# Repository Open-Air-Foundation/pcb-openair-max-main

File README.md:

# AirGradient Open Air Max — Hardware

> KiCad hardware design files for the [AirGradient Open Air Max](https://www.airgradient.com/professional/products/open-air-max/), a professional outdoor air quality monitor.

## Overview

Open Air Max is AirGradient's professional outdoor air quality monitor, designed for autonomous, off-grid operation. It measures PM2.5 (2× Plantower PMS5003), CO₂ (SenseAir Sunlight NDIR, 0–5,000 ppm), TVOCs/NOₓ (Sensirion SGP41), NO₂ (AlphaSense A43F) and O₃ (AlphaSense A431), plus temperature and humidity (Sensirion SHT40), in a UV-resistant, weatherproof ASA enclosure with wall or pole mounting (model O-M-1PPSTON-CE; CE, RoHS, REACH, and FCC certified).

Data is reported over Wi-Fi (2.4 GHz IEEE 802.11 b/g/n) or 4G cellular (LTE Cat 1). Power comes from a 10 W solar panel charging a user-replaceable pack of three 3,500 mAh Li-ion 18650 cells in series (3S), managed by a dedicated battery management system and a low-power design throughout.

This repository contains the monitor's main PCB: the ESP32-C6 MCU, solar/USB-C charging and power path, battery management, and the interfaces the sensor modules and the cellular CE card plug into — complete with schematics, PCB layout, bundled 3D models, and the production output set.

## Design structure

The design is a single 4-layer board (signal / power plane / ground plane / signal) drawn across three schematic sheets:

| Sheet | File | Contents |
|---|---|---|
| Root | `PCB/openair-max/One-Air-Max.kicad_sch` | MCU, power distribution, sensor and CE-card interfaces |
| Battery holder | `PCB/openair-max/Battery-Holder.kicad_sch` | 18650 battery interface and BMS |
| Solar module | `PCB/openair-max/Solar-Module.kicad_sch` | Charger and solar input conditioning |

## Repository structure

```
PCB/
└── openair-max/             # Main PCB (schematic, layout, DRC rules, production/)
libraries/                   # Shared 3D model libraries
├── 3d/                      # STEP models
└── easyeda2kicad/           # easyeda2kicad WRL models
```

## Key components

| Function | Part | Ref |
|---|---|---|
| MCU / Wi-Fi / BLE | ESP32-C6-WROOM-1-N8 | U1 |
| Buck converter | TPS62902 | U2 |
| Hardware watchdog timer | TPL5010 | U3 |
| Battery management system (BMS) | BQ7790512 (BQ76905 family) | U4 |
| Battery charger (solar + USB-C) | BQ25798 | U5 |
| Boost converter | TPS62903 | U6 |
| Power mux / load switch (RC soft-start) | TPS2117 | U7 |
| I²C-to-dual-UART bridge | WK2132 | U8 |
| EEPROM (2 Mbit, optional — DNP) | AT24CM02 | U12 |
| High-side load switches (switched sensor rails) | TPS27081A | U13–U19 |

**Power architecture:** The BQ25798 charger takes two power inputs — the solar cell on **VAC1** and USB-C on **VAC2** — and charges the 3S 18650 pack behind the BQ76905 BMS. The system rail is switched through the TPS2117 with an RC soft-start network to limit inrush current, and a 470 µF bulk capacitor ahead of the load switch provides brownout immunity.

## Plug-in modules

The gas sensors and the cellular option are separate boards that plug into this board's connectors. The assembled Open Air Max (O-M-1PPSTON-CE) carries all of them:

| Module | Repository | Connector on this board |
|---|---|---|
| SUNX CO₂ sensor module (SenseAir Sunlight, UART) | [pcb-module-sunx](https://github.com/Open-Air-Foundation/pcb-module-sunx) | `CO2` — 8-pin Molex PicoBlade: switched 5 V (VOUT2, EN_CO2 = IO5), GND, UART0 (IO0/IO1) |
| SGP41 TVOC/NOₓ sensor module (I²C) | [pcb-module-sgp41](https://github.com/Open-Air-Foundation/pcb-module-sgp41) | `I2C1` / `I2C2` — 1×4 sockets, 2.54 mm: 3.3 V, GND, SCL (IO6), SDA (IO7) |
| SHT4x temperature/humidity sensor module (I²C) | [pcb-module-sht40](https://github.com/Open-Air-Foundation/pcb-module-sht40) | `I2C1` / `I2C2` — the two sockets are identical; one takes the SGP41 module, the other the SHT4x module |
| AlphaSense ADC module — NO₂ (A43F) and O₃ (A431), I²C | [pcb-module-alphasense-adc](https://github.com/Open-Air-Foundation/pcb-module-alphasense-adc) | `NO2` — 8-pin Molex PicoBlade: switched 5 V and 3.3 V (VOUT6/VOUT5, EN_NO2 = IO4), GND, I²C |
| CE card — 4G cellular (LTE Cat 1) | [pcb-module-ce-card](https://github.com/Open-Air-Foundation/pcb-module-ce-card) | `CE1` — 8-pin Molex PicoBlade: switched 5 V and 3.3 V (VOUT4/VOUT3, EN_CE = IO15), power/reset control (IO23, IO21), UART (IO16/IO17) |

The particulate sensors (2× Plantower PMS5003) plug straight into the `PM1`/`PM2` PicoBlade sockets (switched 5 V + UART through the WK2132 bridge) and have no module board of their own. `I2C3` (4-pin, 1.25 mm; I²C) and `IO1` (8-pin PicoBlade: 5 V, 3.3 V, I²C, IO18–IO20) are spare expansion connectors.

## Toolchain

- **KiCad 10** (file format 2026-02). Symbols and footprints are embedded in the design files; all 3D models are bundled in `libraries/` and referenced project-relative — the project opens without any extra library setup.
- **[Fabrication Toolkit](https://github.com/bennymeg/Fabrication-Toolkit)** plugin — generates the Gerber/BOM/CPL production set in JLCPCB-compatible format.
- Active DRC rules are in `PCB/openair-max/One-Air-Max.kicad_dru`; `PCB/openair-max/DRC/JLCPCB.kicad_dru` is a slightly stricter JLCPCB reference template.

## Fabrication

`PCB/openair-max/production/` holds the ready-to-order set for the released version: Gerber zip, BOM, designators, and pick-and-place positions (generated with Fabrication Toolkit, LCSC part numbers for assembly at JLCPCB).

## Versioning & releases

Hardware revisions are tagged on this repository. Per-version release notes — chip-level changes and the matching production file set — are published on the [GitHub Releases](../../releases) page.

## Related repositories

- [firmware-openair-max](https://github.com/Open-Air-Foundation/firmware-openair-max) — ESP32-C6 firmware for this board
- [pcb-module-sunx](https://github.com/Open-Air-Foundation/pcb-module-sunx) — SUNX CO₂ sensor module (SenseAir Sunlight)
- [pcb-module-sgp41](https://github.com/Open-Air-Foundation/pcb-module-sgp41) — SGP41 TVOC/NOₓ sensor module
- [pcb-module-sht40](https://github.com/Open-Air-Foundation/pcb-module-sht40) — SHT4x temperature/humidity sensor module
- [pcb-module-alphasense-adc](https://github.com/Open-Air-Foundation/pcb-module-alphasense-adc) — AlphaSense ADC module (NO₂ / O₃ electrochemical sensors)
- [pcb-module-ce-card](https://github.com/Open-Air-Foundation/pcb-module-ce-card) — 4G cellular extension (CE) card; the assembled Open Air Max includes this card, fitted to the CE1 connector

## License

This is open-source hardware. The design files in this repository are licensed under the
[Creative Commons Attribution-ShareAlike 4.0 International (CC BY-SA 4.0)](https://creativecommons.org/licenses/by-sa/4.0/) license — see [LICENSE](LICENSE).

You are free to use, modify, and manufacture these designs, including commercially, provided you credit AirGradient and share derivative designs under the same license.

## Maintainers

AirGradient hardware team.

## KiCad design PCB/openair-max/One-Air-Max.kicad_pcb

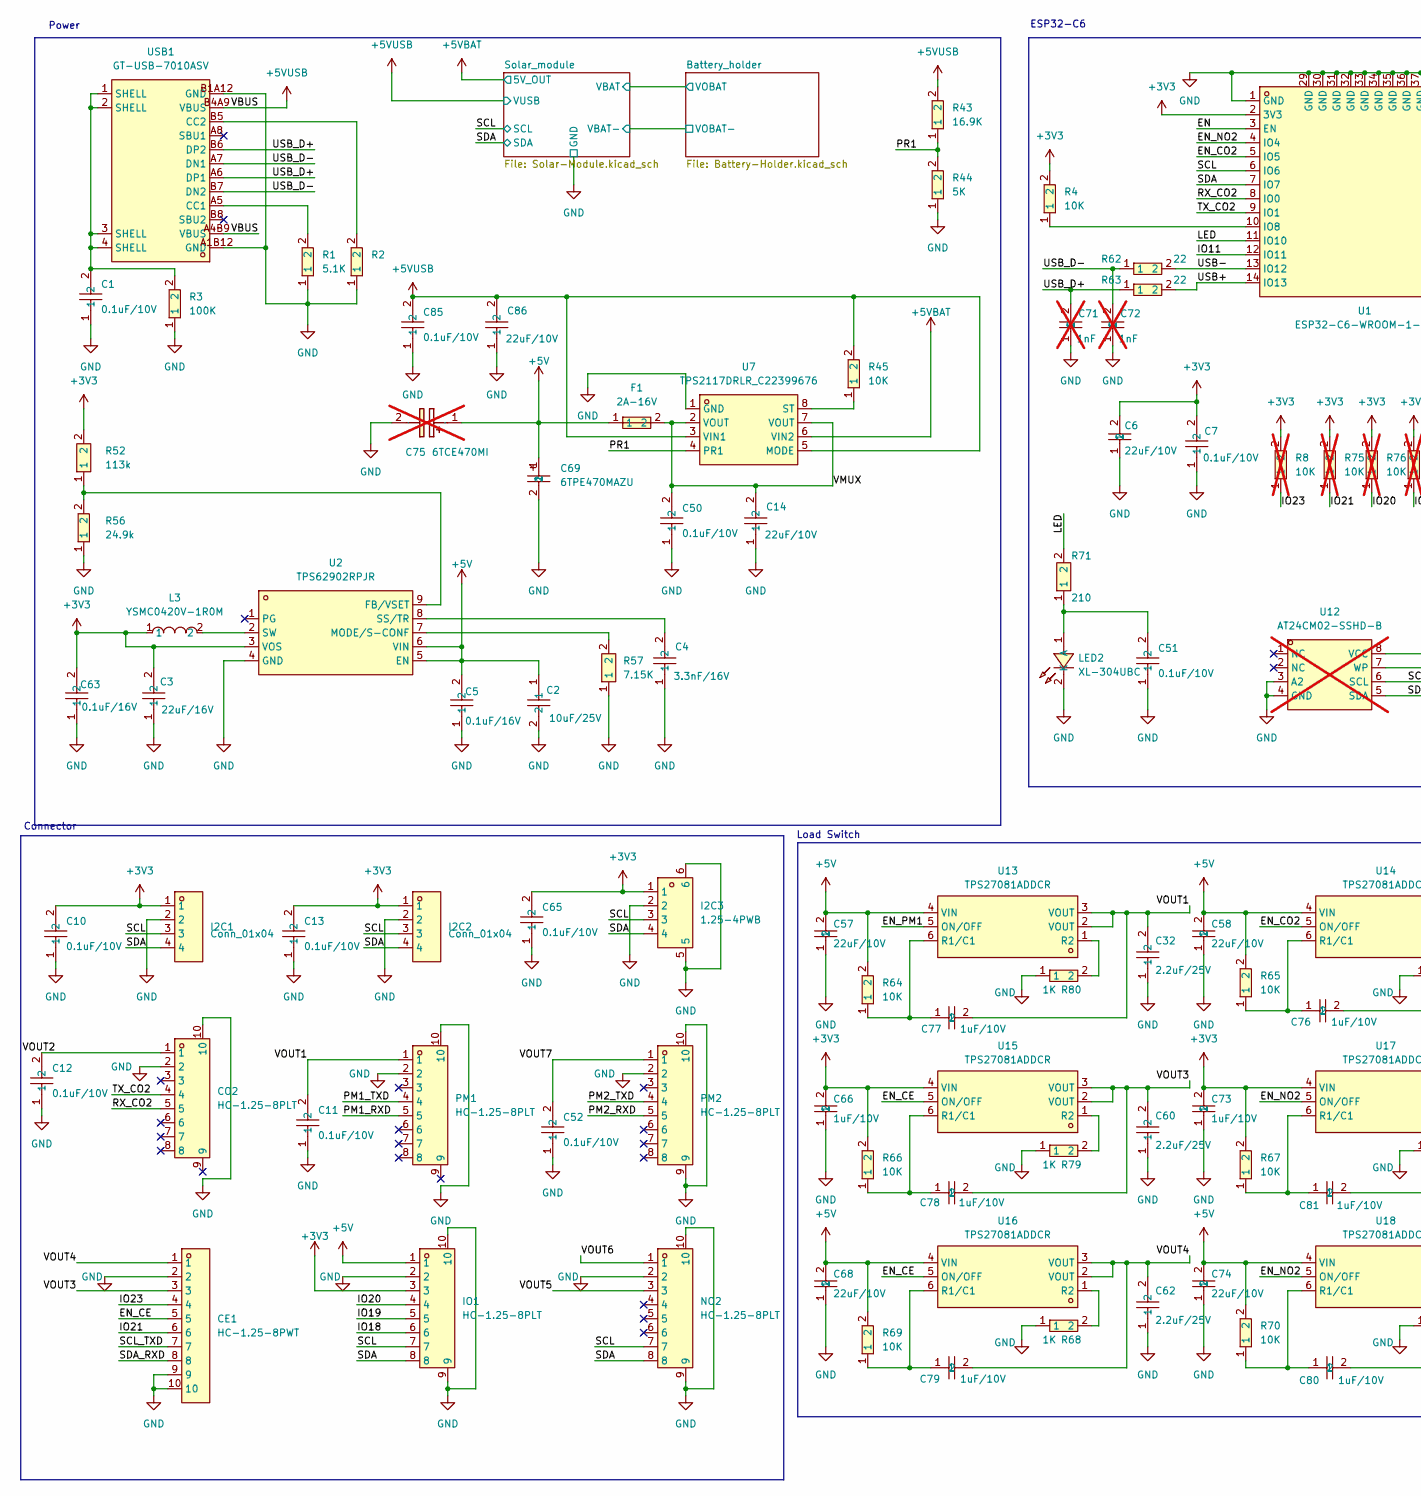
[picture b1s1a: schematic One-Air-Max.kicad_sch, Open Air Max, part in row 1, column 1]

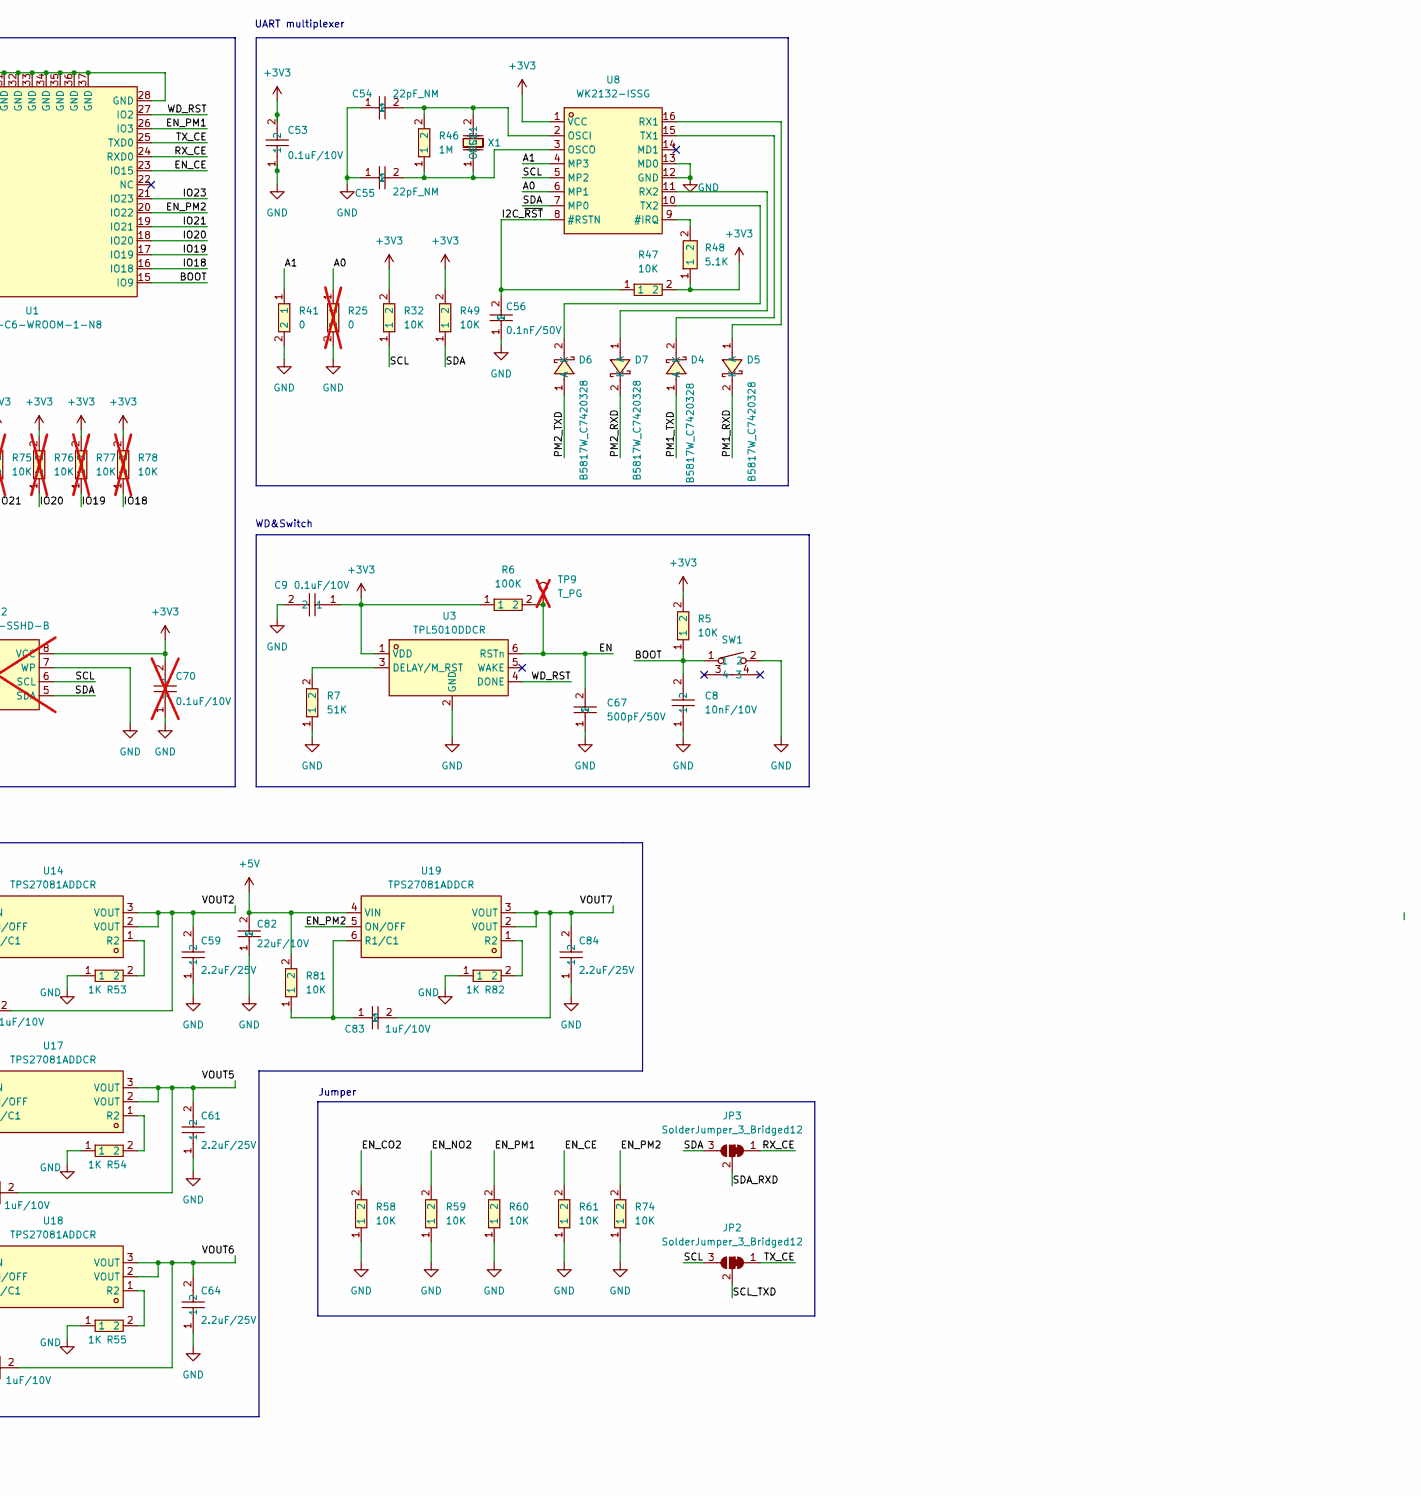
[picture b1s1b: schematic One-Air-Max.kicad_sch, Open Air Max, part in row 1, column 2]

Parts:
C1, C7, C9, C10, C11, C12, C13, C50, C51, C52, C53, C65, C85: 0.1uF/10V; C0402; LCSC Part C309458
C2: 10uF/25V; C0805; LCSC Part C3039694
C3: 22uF/16V; C1206; LCSC Part C7472972
C4: 3.3nF/16V; C0402; LCSC Part C541378
C5, C63: 0.1uF/16V; C0402; LCSC Part C1525
C6: 22uF/10V; C0603; LCSC Part C109447
C8: 10nF/10V; C0402; LCSC Part C541371
C14, C57, C58, C68, C74, C82, C86: 22uF/10V; C0402; LCSC Part C6119813
C32, C59, C60, C61, C62, C64, C84: 2.2uF/25V; C0402; LCSC Part C385032
C54, C55: 22pF_NM; C0402; LCSC Part C1555
C56: 0.1nF/50V; C0402; LCSC Part C106200
C66, C73, C76, C77, C78, C79, C80, C81, C83: 1uF/10V; C0402; LCSC Part C14445
C67: 500pF/50V; C0603; LCSC Part C1624
C69: 6TPE470MAZU; CASE-D_7343; LCSC Part C79114
C70: 0.1uF/10V; C0402; LCSC Part C309458; not fitted
C71, C72: 1nF; C0402; LCSC Part C106205; not fitted
C75: 6TCE470MI; CASE-D_7343; Manufacturer Part 6TCE470MI; not fitted
CE1: HC-1.25-8PWT; CONN-SMD_HC-1.25-8PWT; LCSC Part C2845385
CO2: HC-1.25-8PLT; CONN-SMD_8P-P1.25_HC-1.25-8PLT; LCSC Part C2845394
D4, D5, D6, D7: B5817W_C7420328; SOD-123_L2.7-W1.6-LS3.7-FD; LCSC Part C7420328
F1: 2A-16V; F1206; LCSC Part C2685749
I2C1, I2C2: Conn_01x04; HDR-TH_4P-P2.54-V-F; LCSC Part C2718488
I2C3: 1.25-4PWB; CONN-SMD_1.25-4PWB; LCSC Part C2905011
IO1: HC-1.25-8PLT; CONN-SMD_8P-P1.25_HC-1.25-8PLT; LCSC Part C2845394
JP2, JP3: SolderJumper_3_Bridged12; SolderJumper-3_P1.3mm_Bridged12_RoundedPad1.0x1.5mm
L3: YSMC0420V-1R0M; IND-SMD_L4.0-W4.0_XGL4020; LCSC Part C7433091
LED2: XL-304UBC; LED-TH_BD3.8-P2.54-FD_BLUE; LCSC Part C2895465
NO2: HC-1.25-8PLT; CONN-SMD_8P-P1.25_HC-1.25-8PLT; LCSC Part C2845394
PM1, PM2: HC-1.25-8PLT; CONN-SMD_8P-P1.25_HC-1.25-8PLT; LCSC Part C2845394
R1, R2: 5.1K; R0402; LCSC Part C105872
R3, R6: 100K; R0402; LCSC Part C60491
R4, R5, R32, R45, R49: 10K; R0402; LCSC Part C60490
R7: 51K; R0402; LCSC Part C107229
R8, R75, R76, R77, R78: 10K; R0402; LCSC Part C60490; not fitted
R25: 0; R0603; LCSC Part C100044; not fitted
R41: 0; R0603; LCSC Part C100044
R43: 16.9K; R0402; LCSC Part C163488
R44: 5K; R0603; LCSC Part C862232
R46: 1M; R0402; LCSC Part C327799
R47, R58, R59, R60, R61, R64, R65, R66, R67, R69, R70, R74, R81: 10K; R0402; LCSC Part C327797
R48: 5.1K; R0402; LCSC Part C413002
R52: 113k; R0402; LCSC Part C273332
R53, R54, R55, R68, R79, R80, R82: 1K; R0402; LCSC Part C106235
R56: 24.9k; R0402; LCSC Part C226371
R57: 7.15K; R0603; LCSC Part C861562
R62, R63: 22; R0402; LCSC Part C114765
R71: 210; R0402; LCSC Part C2076880
SW1: TS-1096-A1B2-D2; KEY-TH_TS-1096-A1B2-D2; LCSC Part C492993
TP9: T_PG; TestPoint_Pad_D1.5mm; not fitted
U1: ESP32-C6-WROOM-1-N8; WIRELM-SMD_ESP32-C6-WROOM-1; LCSC Part C5366877
U2: TPS62902RPJR; VQFN-HR-9_L2.0-W1.5-P0.50-TL; LCSC Part C2870154
U3: TPL5010DDCR; SOT-23-6_L2.9-W1.6-P0.95-LS2.8-BR; LCSC Part C473912
U7: TPS2117DRLR_C22399676; SOT-583-8_L2.1-W1.2-P0.50-LS1.6-BL; LCSC Part C22399676
U8: WK2132-ISSG; SSOP-16_L7.2-W5.3-P0.65-LS7.8-BL; LCSC Part C401039
U12: AT24CM02-SSHD-B; SOIC-8_L4.9-W3.9-P1.27-LS6.0-BL; LCSC Part C220680; not fitted
U13, U14, U15, U16, U17, U18, U19: TPS27081ADDCR; SOT-23-6_L2.9-W1.6-P0.95-LS2.8-BR; LCSC Part C128404
USB1: GT-USB-7010ASV; USB-C-SMD_G-SWITCH_GT-USB-7010ASV; LCSC Part C2988369
X1: SMD-5032_2P 14.7456MHZ 20PF 20PPM; OSC-SMD_L5.0-W3.2; LCSC Part C362355

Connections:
+3V3: C3.2, C6.2, C7.2, C9.1, C10.2, C13.2, C53.2, C63.2, C65.2, C66.2, C70.2, C73.2, I2C1.1, I2C2.1, I2C3.1, IO1.3, L3.1, R4.2, R5.2, R6.1, R8.2, R32.2, R47.2, R48.1, R49.2, R52.2, R66.2, R67.2, R75.2, R76.2, R77.2, R78.2, U1.2 (3V3), U2.3 (VOS), U3.1 (VDD), U8.1 (VCC), U12.8 (VCC), U15.4 (VIN), U17.4 (VIN); also elsewhere on the board
+5V: C2.1, C5.2, C57.2, C58.2, C68.2, C69.1, C74.2, C75.1 (+), C82.2, F1.1, IO1.1, R64.2, R65.2, R69.2, R70.2, R81.2, U2.5 (EN), U2.6 (VIN), U13.4 (VIN), U14.4 (VIN), U16.4 (VIN), U18.4 (VIN), U19.4 (VIN)
+5VBAT: U7.6 (VIN2); also elsewhere on the board
+5VUSB: C85.2, C86.2, R43.2, R45.2, U7.3 (VIN1), U7.5 (MODE), USB1.A4B9 (VBUS), USB1.B4A9 (VBUS); also elsewhere on the board
/A0: R25.1, U8.6 (MP1)
/A1: R41.1, U8.4 (MP3)
/BOOT: C8.2, R5.1, SW1.1, U1.15 (IO9)
/EN: C67.2, R6.2, TP9.1 (1_1), U1.3 (EN), U3.6 (RSTn)
/EN_CE: CE1.5, R61.2, U1.23 (IO15), U15.5 (ON/OFF), U16.5 (ON/OFF)
/EN_CO2: R58.2, U1.5 (IO5), U14.5 (ON/OFF)
/EN_NO2: R59.2, U1.4 (IO4), U17.5 (ON/OFF), U18.5 (ON/OFF)
/EN_PM1: R60.2, U1.26 (IO3), U13.5 (ON/OFF)
/EN_PM2: R74.2, U1.20 (IO22), U19.5 (ON/OFF)
/I2C_~RST: C56.2, R47.1, U8.8 (#RSTN)
/IO11: U1.12 (IO11)
/IO18: IO1.6, R78.1, U1.16 (IO18)
/IO19: IO1.5, R77.1, U1.17 (IO19)
/IO20: IO1.4, R76.1, U1.18 (IO20)
/IO21: CE1.6, R75.1, U1.19 (IO21)
/IO23: CE1.4, R8.1, U1.21 (IO23)
/LED: R71.2, U1.11 (IO10)
/PM1_RXD: D5.2 (K), PM1.5
/PM1_TXD: D4.1 (A), PM1.4
/PM2_RXD: D7.2 (K), PM2.5
/PM2_TXD: D6.1 (A), PM2.4
/PR1: R43.1, R44.2, U7.4 (PR1)
/RX_CE: JP3.1 (A), U1.24 (RXD0)
/RX_CO2: CO2.5, U1.8 (IO0)
/SCL: I2C1.3, I2C2.3, I2C3.3, IO1.7, JP2.3 (B), NO2.7, R32.1, U1.6 (IO6), U8.5 (MP2), U12.6 (SCL); also elsewhere on the board
/SCL_TXD: CE1.7, JP2.2 (C)
/SDA: I2C1.4, I2C2.4, I2C3.4, IO1.8, JP3.3 (B), NO2.8, R49.1, U1.7 (IO7), U8.7 (MP0), U12.5 (SDA); also elsewhere on the board
/SDA_RXD: CE1.8, JP3.2 (C)
/TX_CE: JP2.1 (A), U1.25 (TXD0)
/TX_CO2: CO2.4, U1.9 (IO1)
/USB+: R63.2, U1.14 (IO13)
/USB-: R62.2, U1.13 (IO12)
/USB_D+: C71.2, R63.1, USB1.A6 (DP1), USB1.B6 (DP2)
/USB_D-: C72.2, R62.1, USB1.A7 (DN1), USB1.B7 (DN2)
/VMUX: C14.2, C50.2, F1.2, U7.2 (VOUT), U7.7 (VOUT)
/VOUT1: C11.2, C32.2, C77.2, PM1.1, U13.2 (VOUT), U13.3 (VOUT)
/VOUT2: C12.2, C59.2, C76.2, CO2.1, U14.2 (VOUT), U14.3 (VOUT)
/VOUT3: C60.2, C78.2, CE1.3, U15.2 (VOUT), U15.3 (VOUT)
/VOUT4: C62.2, C79.2, CE1.1, U16.2 (VOUT), U16.3 (VOUT)
/VOUT5: C61.2, C81.2, NO2.3, U17.2 (VOUT), U17.3 (VOUT)
/VOUT6: C64.2, C80.2, NO2.1, U18.2 (VOUT), U18.3 (VOUT)
/VOUT7: C52.2, C83.2, C84.2, PM2.1, U19.2 (VOUT), U19.3 (VOUT)
/WD_RST: U1.27 (IO2), U3.4 (DONE)
GND: C1.1, C2.2, C3.1, C4.1, C5.1, C6.1, C7.1, C8.1, C9.2, C10.1, C11.1, C12.1, C13.1, C14.1, C32.1, C50.1, C51.1, C52.1, C53.1, C54.1, C55.1, C56.1, C57.1, C58.1, C59.1, C60.1, C61.1, C62.1, C63.1, C64.1, C65.1, C66.1, C67.1, C68.1, C69.2, C70.1, C71.1, C72.1, C73.1, C74.1, C75.2 (-), C82.1, C84.1, C85.1, C86.1, CE1.2, CE1.9, CE1.10, CO2.2, CO2.10, I2C1.2, I2C2.2, I2C3.2, I2C3.5, I2C3.6, IO1.2, IO1.9, IO1.10, LED2.2 (K), NO2.2, NO2.9, NO2.10, PM1.2, PM1.10, PM2.2, PM2.9, PM2.10, R1.1, R2.1, R3.1, R7.1, R25.2, R41.2, R44.1, R53.1, R54.1, R55.1, R56.1, R57.1, R58.1, R59.1, R60.1, R61.1, R68.1, R74.1, R79.1, R80.1, R82.1, SW1.2, U1.1 (GND), U1.28 (GND), U1.29 (GND), U1.30 (GND), U1.31 (GND), U1.32 (GND), U1.33 (GND), U1.34 (GND), U1.35 (GND), U1.36 (GND), U1.37 (GND), U2.4 (GND), U3.2 (GND), U7.1 (GND), U8.12 (GND), U8.13 (MD0), U12.3 (A2), U12.4 (GND), U12.7 (WP), USB1.A1B12 (GND), USB1.B1A12 (GND); also elsewhere on the board
unnamed: C1.2, R3.2, USB1.1 (SHELL), USB1.2 (SHELL), USB1.3 (SHELL), USB1.4 (SHELL)
unnamed: D4.2 (K), U8.15 (TX1)
unnamed: D5.1 (A), U8.16 (RX1)
unnamed: D6.2 (K), U8.10 (TX2)
unnamed: D7.1 (A), U8.11 (RX2)
unnamed: C51.2, LED2.1 (A), R71.1
unnamed: R4.1, U1.10 (IO8)
unnamed: R52.1, R56.2, U2.9 (FB/VSET)
unnamed: R57.2, U2.7 (MODE/S-CONF)
unnamed: C4.2, U2.8 (SS/TR)
unnamed: L3.2, U2.2 (SW)
unnamed: R7.2, U3.3 (DELAY/M_RST)
unnamed: R45.1, U7.8 (ST)
unnamed: R48.2, U8.9 (#IRQ)
unnamed: C54.2, R46.2, U8.2 (OSCI), X1.2 (OSC2)
unnamed: C55.2, R46.1, U8.3 (OSCO), X1.1 (OSC1)
unnamed: C77.1, R64.1, U13.6 (R1/C1)
unnamed: R80.2, U13.1 (R2)
unnamed: C76.1, R65.1, U14.6 (R1/C1)
unnamed: R53.2, U14.1 (R2)
unnamed: C78.1, R66.1, U15.6 (R1/C1)
unnamed: R79.2, U15.1 (R2)
unnamed: C79.1, R69.1, U16.6 (R1/C1)
unnamed: R68.2, U16.1 (R2)
unnamed: C81.1, R67.1, U17.6 (R1/C1)
unnamed: R54.2, U17.1 (R2)
unnamed: C80.1, R70.1, U18.6 (R1/C1)
unnamed: R55.2, U18.1 (R2)
unnamed: C83.1, R81.1, U19.6 (R1/C1)
unnamed: R82.2, U19.1 (R2)
unnamed: R1.2, USB1.A5 (CC1)
unnamed: R2.2, USB1.B5 (CC2)

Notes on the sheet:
WD&Switch
Load Switch
Power
UART multiplexer
Connector
Jumper
ESP32-C6

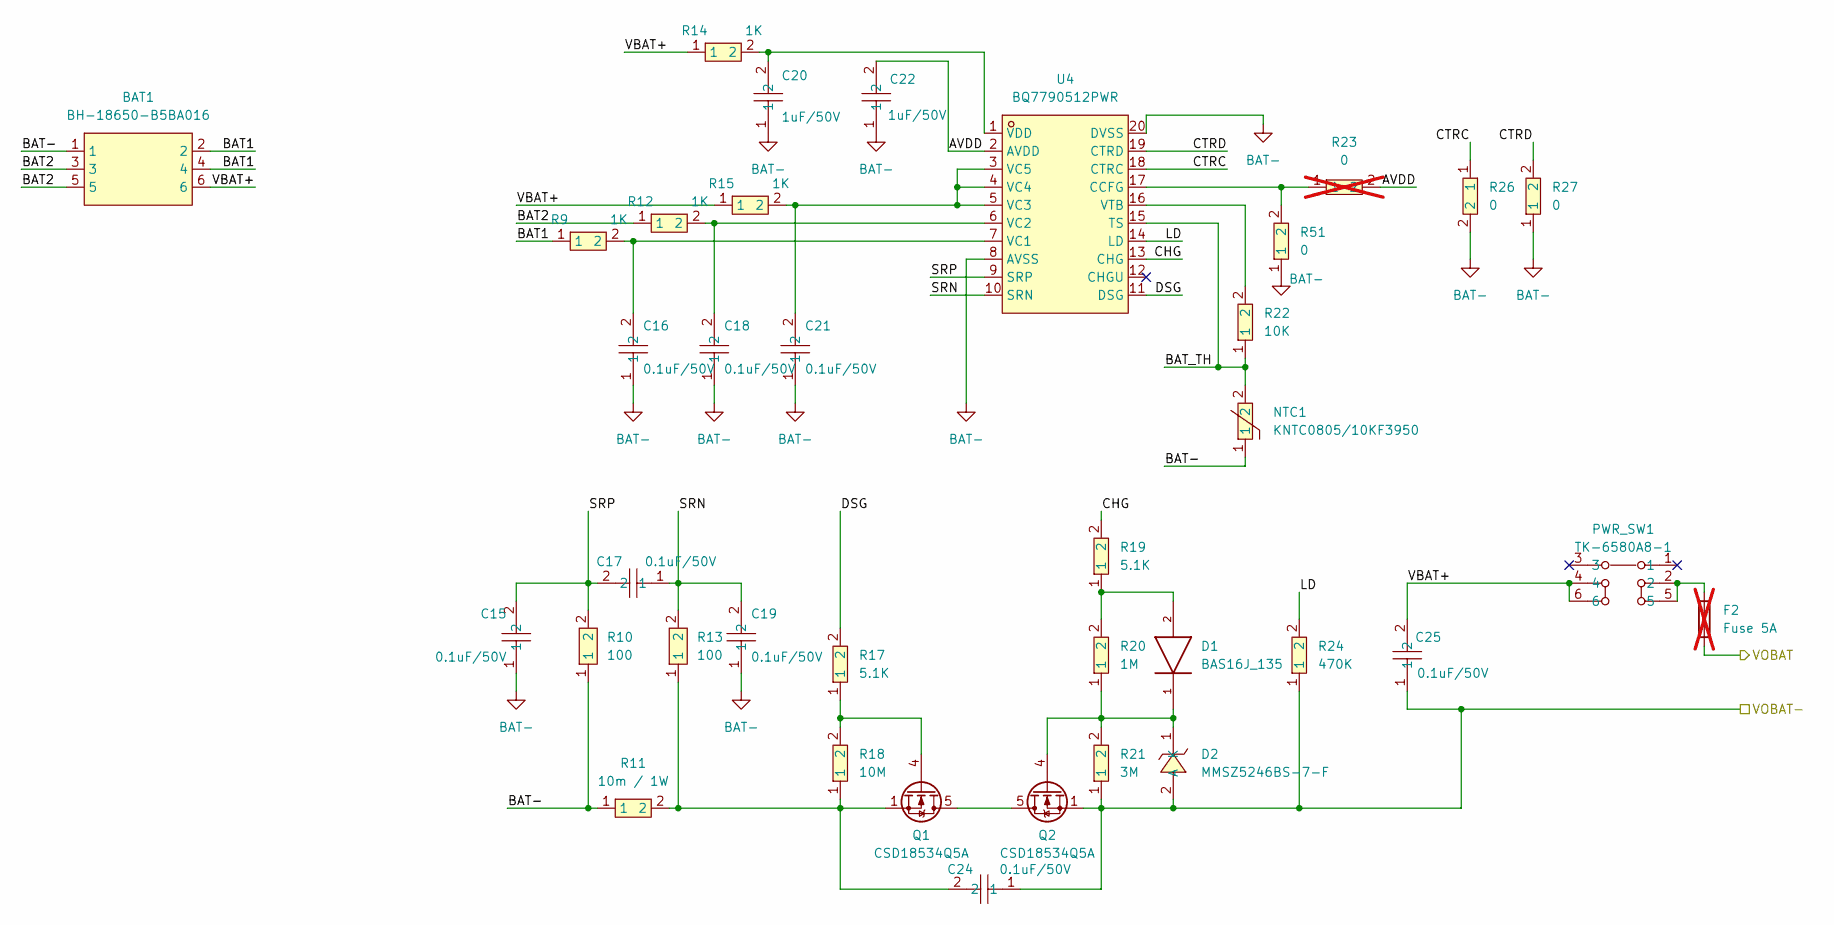
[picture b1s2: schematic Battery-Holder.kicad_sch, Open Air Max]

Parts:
BAT1: BH-18650-B5BA016; BAT-SMD_BH-18650-B5BA016; LCSC Part C19184086
C15, C16, C17, C18, C19, C21, C24, C25: 0.1uF/50V; C0603; LCSC Part C14663
C20, C22: 1uF/50V; C0402; LCSC Part C7500380
D1: BAS16J_135; SOD2512X80N; MOUSER_PART_NUMBER 771-BAS16J135
D2: MMSZ5246BS-7-F; SOD-323_L1.8-W1.3-LS2.5-RD; LCSC Part C151819
F2: Fuse 5A; PCB_fuse; not fitted
NTC1: KNTC0805/10KF3950; R0805; LCSC Part C2892549
PWR_SW1: TK-6580A8-1; SW-TH_TK-6580A8-1; LCSC Part C528772
Q1, Q2: CSD18534Q5A; PQFN-8_L5.8-W4.9-P1.27-LS6.0-BL
R9, R12, R14, R15: 1K; R0402; LCSC Part C851849
R10, R13: 100; R0402; LCSC Part C606168
R11: 10m / 1W; R2512; LCSC Part C705061
R17, R19: 5.1K; R0603; LCSC Part C105580
R18: 10M; R0603; LCSC Part C114606
R20: 1M; R0603; LCSC Part C105578
R21: 3M; R0603; LCSC Part C126361
R22: 10K; R0603; LCSC Part C98220
R23: 0; R0603; LCSC Part C100044; not fitted
R24: 470K; R0603; LCSC Part C114622
R26, R27, R51: 0; R0603; LCSC Part C100044
U4: BQ7790512PWR; TSSOP-20_L6.5-W4.4-P0.65-LS6.4-BL; LCSC Part C555146

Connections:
/Battery_holder/AVDD: C22.2, R23.2, U4.2 (AVDD)
/Battery_holder/BAT1: BAT1.2, BAT1.4, R9.1
/Battery_holder/BAT2: BAT1.3, BAT1.5, R12.1
/Battery_holder/BAT_TH: NTC1.2, R22.1, U4.15 (TS)
/Battery_holder/CHG: R19.2, U4.13 (CHG)
/Battery_holder/CTRC: R26.1, U4.18 (CTRC)
/Battery_holder/CTRD: R27.2, U4.19 (CTRD)
/Battery_holder/DSG: R17.2, U4.11 (DSG)
/Battery_holder/LD: R24.2, U4.14 (LD)
/Battery_holder/SRN: C17.1, C19.2, R13.2, U4.10 (SRN)
/Battery_holder/SRP: C15.2, C17.2, R10.2, U4.9 (SRP)
/Battery_holder/VBAT+: BAT1.6, C25.2, PWR_SW1.4, PWR_SW1.6, R14.1, R15.1
/Solar_module/VBAT: F2.1; also elsewhere on the board
BAT-: BAT1.1, C15.1, C16.1, C18.1, C19.1, C20.1, C21.1, C22.1, NTC1.1, R10.1, R11.1, R26.2, R27.1, R51.1, U4.8 (AVSS), U4.20 (DVSS)
unnamed: C24.2, Q1.1 (S), Q1.2 (S), Q1.3 (S), R11.2, R13.1, R18.1
unnamed: D1.2, R19.1, R20.2
unnamed: D1.1, D2.1 (K), Q2.4 (G), R20.1, R21.2
unnamed: F2.2, PWR_SW1.2, PWR_SW1.5
unnamed: Q1.5 (D), Q1.6 (S), Q1.7 (S), Q1.8 (S), Q2.5 (D), Q2.6 (S), Q2.7 (S), Q2.8 (S)
unnamed: Q1.4 (G), R17.1, R18.2
unnamed: R23.1, R51.2, U4.17 (CCFG)
unnamed: C16.2, R9.2, U4.7 (VC1)
unnamed: C18.2, R12.2, U4.6 (VC2)
unnamed: C21.2, R15.2, U4.3 (VC5), U4.4 (VC4), U4.5 (VC3)
unnamed: C20.2, R14.2, U4.1 (VDD)
unnamed: R22.2, U4.16 (VTB)
PGND: C24.1, C25.1, D2.2 (A), Q2.1 (S), Q2.2 (S), Q2.3 (S), R21.1, R24.1; also elsewhere on the board

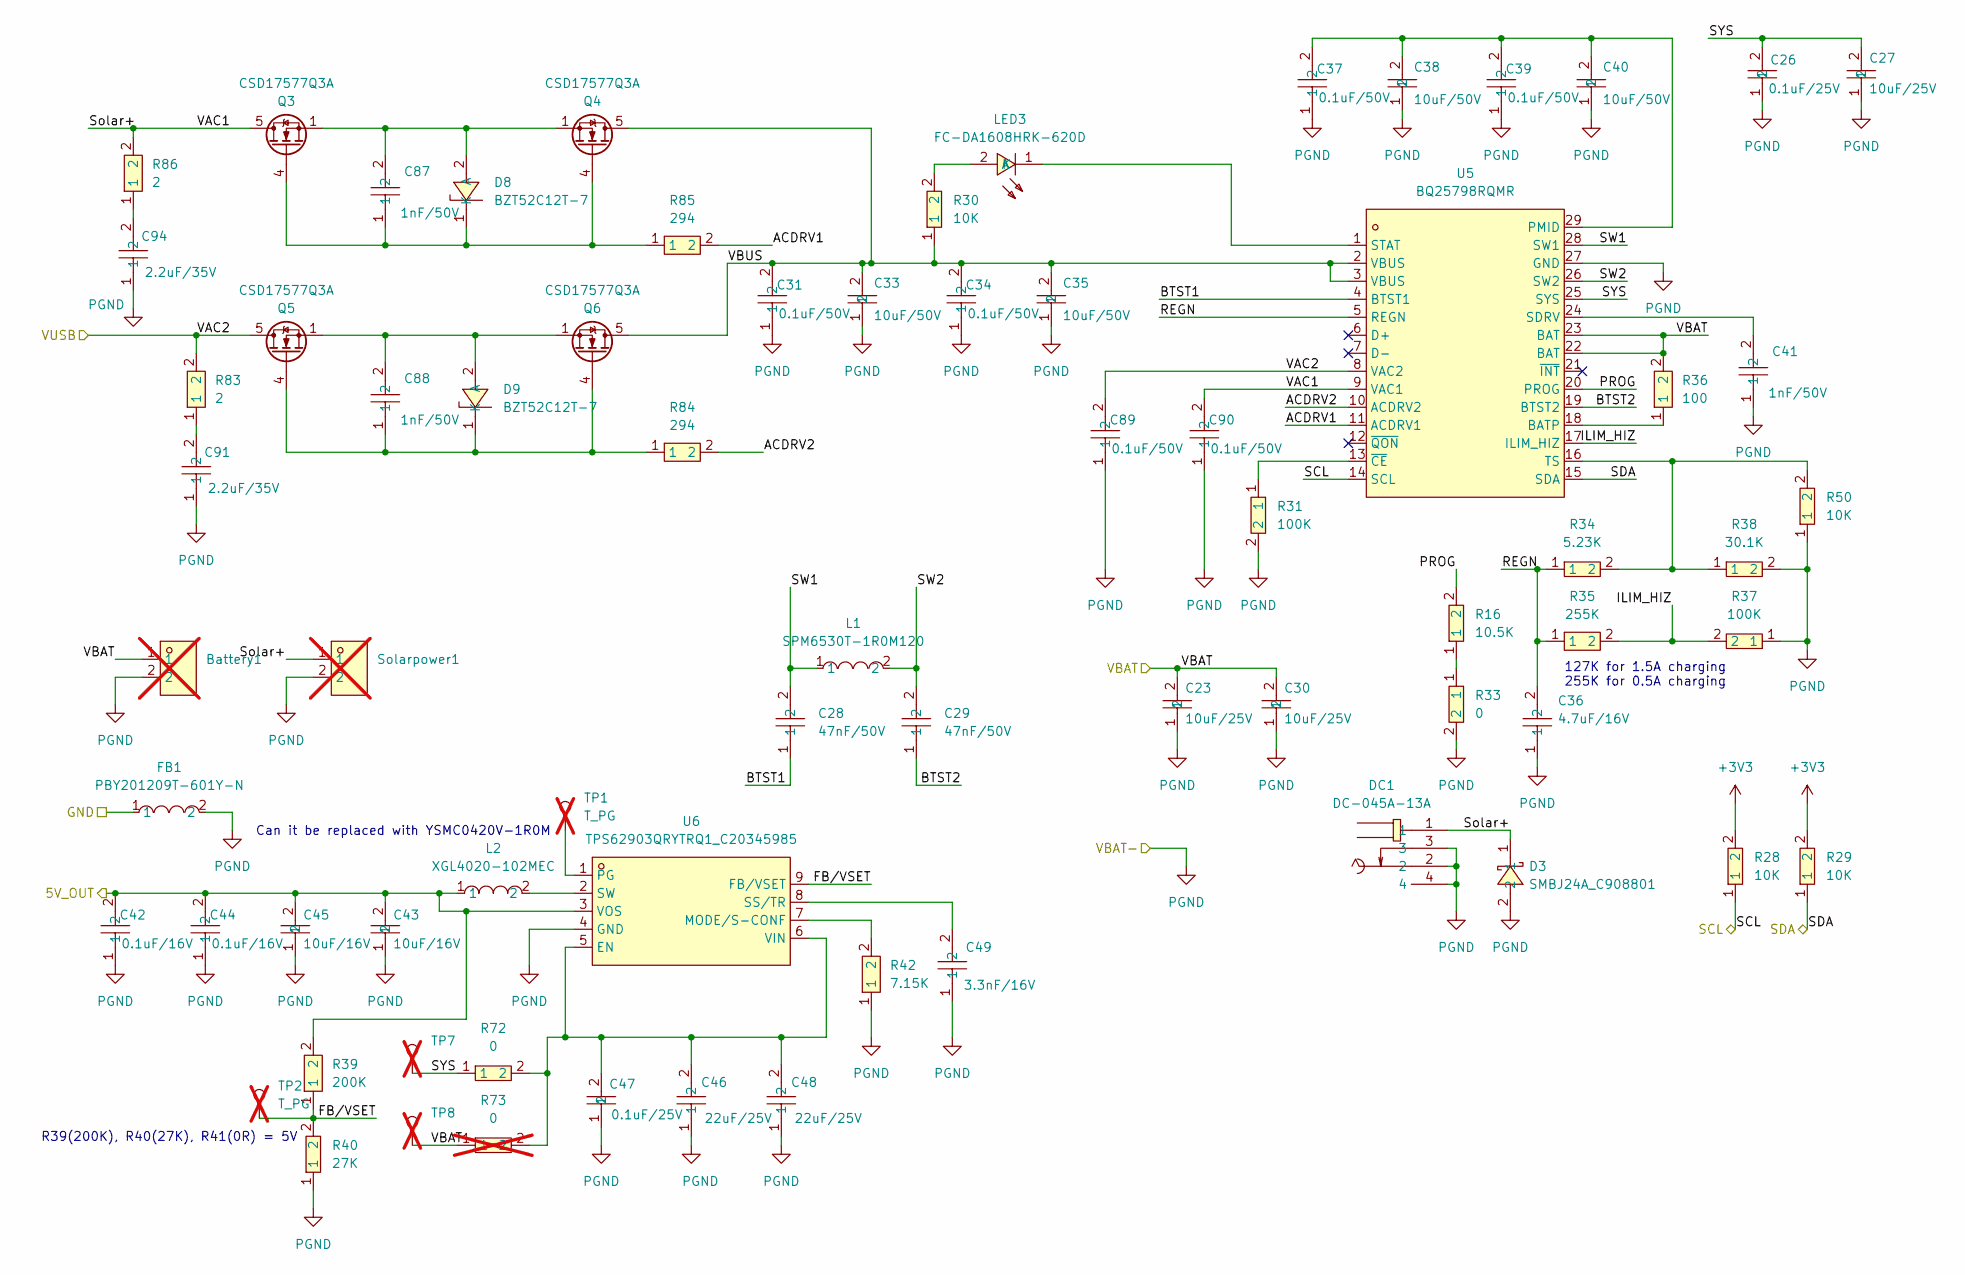
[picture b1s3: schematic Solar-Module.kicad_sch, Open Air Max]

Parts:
Battery1: ZX-PM2.54-1-2PY; HDR-TH_2P-P2.54-V-F; LCSC Part C7499322; not fitted
C23, C27, C30: 10uF/25V; C1206; LCSC Part C9807
C26, C47: 0.1uF/25V; C0402; LCSC Part C100072
C28, C29: 47nF/50V; C0402; LCSC Part C272875
C31, C34, C37, C39, C89, C90: 0.1uF/50V; C0402; LCSC Part C77020
C33, C35, C38, C40: 10uF/50V; C1206; LCSC Part C13585
C36: 4.7uF/16V; C0603; LCSC Part C22399629
C41, C87, C88: 1nF/50V; C0402; LCSC Part C77018
C42, C44: 0.1uF/16V; C0402; LCSC Part C1525
C43, C45: 10uF/16V; C1206; LCSC Part C109464
C46, C48: 22uF/25V; C0805; LCSC Part C602037
C49: 3.3nF/16V; C0402; LCSC Part C541378
C91, C94: 2.2uF/35V; C0402; LCSC Part C6119793
D3: SMBJ24A_C908801; SMB_L4.4-W3.6-LS5.3-RD; LCSC Part C908801
D8, D9: BZT52C12T-7; SOD-523_L1.2-W0.8-LS1.6-RD; LCSC Part C507911
DC1: DC-045A-13A; DC-IN-SMD_DC-045A-13A; LCSC Part C707277
FB1: PBY201209T-601Y-N; L0805; LCSC Part C108304
L1: SPM6530T-1R0M120; IND-SMD_L7.1-W6.5-P5.60; LCSC Part C87572
L2: XGL4020-102MEC; IND-SMD_L4.0-W4.0_XAL4030-332MEC; LCSC Part C5357696
LED3: FC-DA1608HRK-620D; LED0603-RD_RED; LCSC Part C84263
Q3, Q4, Q5, Q6: CSD17577Q3A; VSON-8_3.3x3.3mm_P0.65mm_NexFET; LCSC Part C201632
R16: 10.5K; R0603; LCSC Part C137808
R28, R29, R30, R50: 10K; R0402; LCSC Part C60490
R31, R37: 100K; R0402; LCSC Part C60491
R33, R72: 0; R0603; LCSC Part C100044
R34: 5.23K; R0603; LCSC Part C185317
R35: 255K; R0603; LCSC Part C295887
R36: 100; R0402; LCSC Part C606168
R38: 30.1K; R0603; LCSC Part C137745
R39: 200K; R0402; LCSC Part C606170
R40: 27K; R0603; LCSC Part C114614
R42: 7.15K; R0603; LCSC Part C861562
R73: 0; R0603; LCSC Part C100044; not fitted
R83, R86: 2; R0402; LCSC Part C514778
R84, R85: 294; R0402; LCSC Part C477682
Solarpower1: ZX-PM2.54-1-2PY; HDR-TH_2P-P2.54-V-F; LCSC Part C7499322; not fitted
TP1, TP2, TP7, TP8: T_PG; TestPoint_Pad_D1.5mm; not fitted
U5: BQ25798RQMR; QFN-29_L4.0-W4.0-P0.40-TL-BQ25792RQMR; LCSC Part C2876593
U6: TPS62903QRYTRQ1_C20345985; VQFNHR-9_L2.2-W2.0_TPS62993QRYTRQ1; LCSC Part C20345985

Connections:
+3V3: R28.2, R29.2; also elsewhere on the board
+5VBAT: C42.2, C43.2, C44.2, C45.2, L2.1, R39.2, U6.3 (VOS); also elsewhere on the board
+5VUSB: C89.2, Q5.5 (D), R83.2, U5.8 (VAC2); also elsewhere on the board
/SCL: R28.1, U5.14 (SCL); also elsewhere on the board
/SDA: R29.1, U5.15 (SDA); also elsewhere on the board
/Solar_module/ACDRV1: R85.2, U5.11 (ACDRV1)
/Solar_module/ACDRV2: R84.2, U5.10 (ACDRV2)
/Solar_module/BTST1: C28.1, U5.4 (BTST1)
/Solar_module/BTST2: C29.1, U5.19 (BTST2)
/Solar_module/FB/VSET: R39.1, R40.2, TP2.1 (1_1), U6.9 (FB/VSET)
/Solar_module/ILIM_HIZ: R35.2, R37.2, U5.17 (ILIM_HIZ)
/Solar_module/PROG: R16.2, U5.20 (PROG)
/Solar_module/REGN: C36.2, R34.1, R35.1, U5.5 (REGN)
/Solar_module/SW1: C28.2, L1.1, U5.28 (SW1)
/Solar_module/SW2: C29.2, L1.2, U5.26 (SW2)
/Solar_module/SYS: C26.2, C27.2, R72.1, TP7.1 (1_1), U5.25 (SYS)
/Solar_module/Solar+: C90.2, D3.1, DC1.1, Q3.5 (D), R86.2, Solarpower1.1, U5.9 (VAC1)
/Solar_module/VBAT: Battery1.1, C23.2, C30.2, R36.2, R73.1, TP8.1 (1_1), U5.22 (BAT), U5.23 (BAT); also elsewhere on the board
/Solar_module/VBUS: C31.2, C33.2, C34.2, C35.2, Q4.5 (D), Q6.5 (D), R30.1, U5.2 (VBUS), U5.3 (VBUS)
GND: FB1.1; also elsewhere on the board
unnamed: C91.2, R83.1
unnamed: C94.2, R86.1
unnamed: C87.2, D8.2 (A), Q3.1 (S), Q3.2 (S), Q3.3 (S), Q4.1 (S), Q4.2 (S), Q4.3 (S)
unnamed: C87.1, D8.1 (K), Q3.4 (G), Q4.4 (G), R85.1
unnamed: C88.2, D9.2 (A), Q5.1 (S), Q5.2 (S), Q5.3 (S), Q6.1 (S), Q6.2 (S), Q6.3 (S)
unnamed: C88.1, D9.1 (K), Q5.4 (G), Q6.4 (G), R84.1
unnamed: LED3.2 (A), R30.2
unnamed: LED3.1 (K), U5.1 (STAT)
unnamed: R16.1, R33.1
unnamed: R36.1, U5.18 (BATP)
unnamed: C37.2, C38.2, C39.2, C40.2, U5.29 (PMID)
unnamed: C41.2, U5.24 (SDRV)
unnamed: R34.2, R38.1, R50.2, U5.16 (TS)
unnamed: R31.1, U5.13 (~CE)
unnamed: C46.2, C47.2, C48.2, R72.2, R73.2, U6.5 (EN), U6.6 (VIN)
unnamed: R42.2, U6.7 (MODE/S-CONF)
unnamed: TP1.1 (1_1), U6.1 (PG)
unnamed: C49.2, U6.8 (SS/TR)
unnamed: L2.2, U6.2 (SW)
PGND: Battery1.2, C23.1, C26.1, C27.1, C30.1, C31.1, C33.1, C34.1, C35.1, C36.1, C37.1, C38.1, C39.1, C40.1, C41.1, C42.1, C43.1, C44.1, C45.1, C46.1, C47.1, C48.1, C49.1, C89.1, C90.1, C91.1, C94.1, D3.2, DC1.2, DC1.3, DC1.4, FB1.2, R31.2, R33.2, R37.1, R38.2, R40.1, R42.1, R50.1, Solarpower1.2, U5.27 (GND), U6.4 (GND); also elsewhere on the board

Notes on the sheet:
Can it be replaced with YSMC0420V-1R0M
R39(200K), R40(27K), R41(0R) = 5V
127K for 1.5A charging 255K for 0.5A charging
